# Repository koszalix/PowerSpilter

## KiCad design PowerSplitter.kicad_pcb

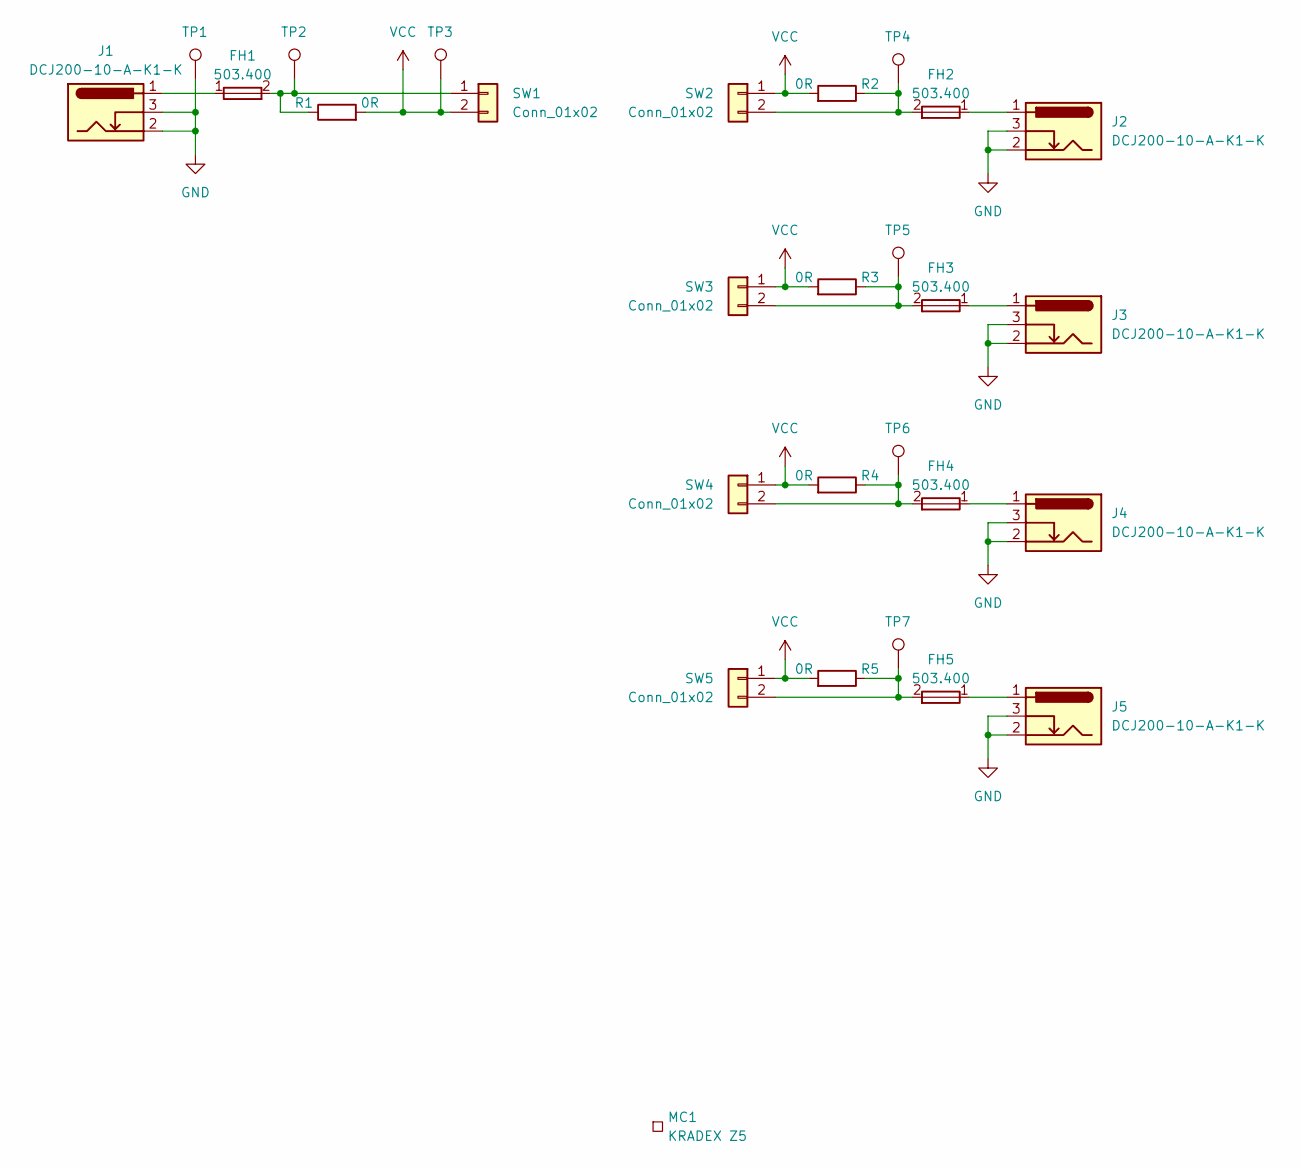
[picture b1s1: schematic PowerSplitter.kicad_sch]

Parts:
FH1, FH2, FH3, FH4, FH5: 503.400; ESKA_503.400; MPN 503.400
J1, J2, J3, J4, J5: DCJ200-10-A-K1-K; GCT-DCJ200-10-A-K1-K; Nominal Voltage 20V DC; MPN DCJ200-10-A-K1-K
MC1: KRADEX Z5; z5; MPN Z5
R1, R2, R3, R4, R5: 0R; R_1206_3216Metric_Pad1.30x1.75mm_HandSolder
SW1, SW2, SW3, SW4, SW5: Conn_01x02; SolderWire-1.5sqmm_1x02_P6mm_D1.7mm_OD3mm_Relief2x
TP1, TP2, TP3, TP4, TP5, TP6, TP7: TestPoint; TestPoint_Pad_D1.0mm

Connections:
GND: J1.2, J1.3, J2.2, J2.3, J3.2, J3.3, J4.2, J4.3, J5.2, J5.3, TP1.1
unnamed: FH1.1, J1.1
unnamed: FH2.1, J2.1
unnamed: FH3.1, J3.1
unnamed: FH4.1, J4.1
unnamed: FH5.1, J5.1
unnamed: FH1.2, R1.1, SW1.1, TP2.1
unnamed: FH2.2, R2.1, SW2.2, TP4.1
unnamed: FH3.2, R3.1, SW3.2, TP5.1
unnamed: FH4.2, R4.1, SW4.2, TP6.1
unnamed: FH5.2, R5.1, SW5.2, TP7.1
VCC: R1.2, R2.2, R3.2, R4.2, R5.2, SW1.2, SW2.1, SW3.1, SW4.1, SW5.1, TP3.1

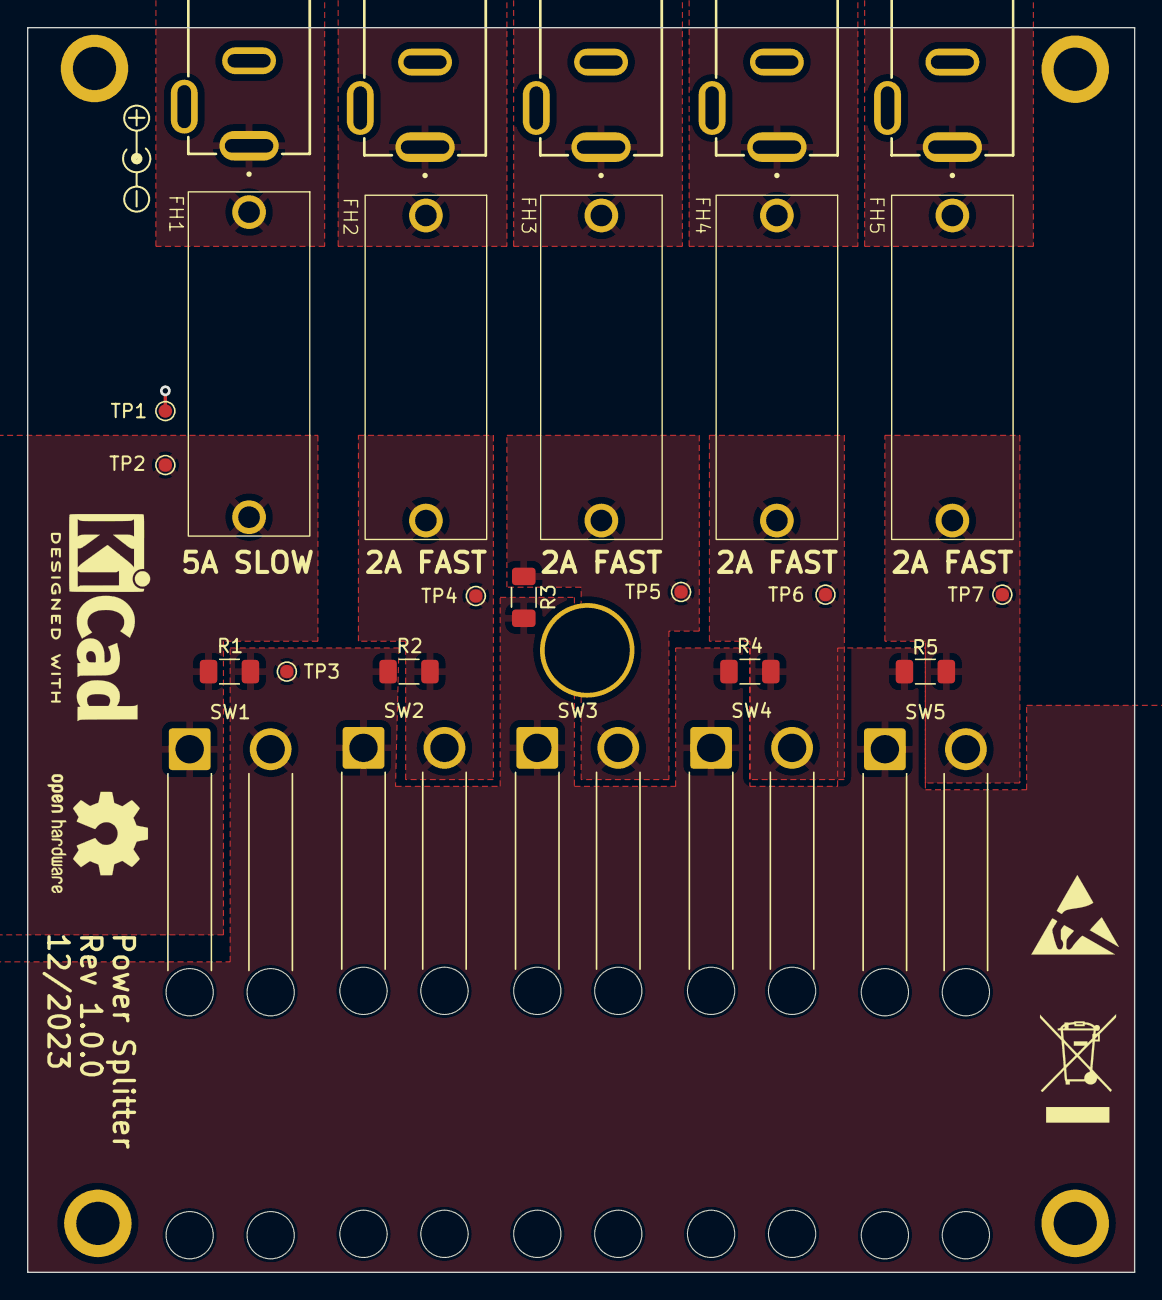
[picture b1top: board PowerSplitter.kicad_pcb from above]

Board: 2 copper layers, 82.0 x 92.2 mm, 28 parts (0 on the bottom side), 12 nets.

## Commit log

2024-03-21 Route PCB
